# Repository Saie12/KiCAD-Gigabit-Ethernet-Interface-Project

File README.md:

# 🚀 High-Speed Gigabit Ethernet Interface

Welcome! This repository contains the complete hardware design files for a custom-built, 6-layer Gigabit Ethernet interface board.

The design is centered around the powerful **STM32F746NGH6** (an ARM Cortex-M7 MCU) and the **DP83867IR** Gigabit PHY. The entire layout was planned to meet strict high-speed design rules, featuring a robust multi-rail power supply and controlled impedance routing for 1Gbps performance.

## 🛠️ Key Features & Components

* **Brain (MCU):** `STM32F746NGH6` (ARM Cortex-M7)
* **Translator (PHY):** `DP83867IRPAPT` (10/100/1000 Mbps Gigabit PHY)
* **Data Interface:** `RGMII`
* **Port (Connector):** `ARJM11D7-502-AB-EW2` (A shielded Gigabit MagJack with integrated LEDs)
* **Power Supply:** 5V USB-C input, feeding a "power tree" of four independent LDOs for ultra-clean `+3.3V`, `+2.5V`, `+1.8V`, and `+1.1V` rails.
* **PCB:** Custom 6-layer, 80x50mm board with controlled impedance routing.
* **Debug:** Standard 10-pin ARM SWD (Serial Wire Debug) header.

## ✅ Hardware Project Status: Complete!

This repository covers the complete hardware design and manufacturing file generation. All phases of the hardware build are finished.

* ✅ **Phase 1: Component Selection**
    * *Selected and verified the core MCU, PHY, MagJack, and all power components for Gigabit-speed requirements.*
* ✅ **Phase 2: Schematic Design**
    * *Created the full electronic blueprint, connecting all components and defining all power and signal nets.*
* ✅ **Phase 3: Pre-Layout Checks**
    * *Ran a full Electrical Rules Check (ERC) and assigned all physical component footprints.*
* ✅ **Phase 4: PCB Layout**
    * *Designed the 6-layer stackup, floorplanned all components, poured all ground and power planes, and hand-routed all 17 critical high-speed differential and RGMII traces.*
* ✅ **Phase 5: Manufacturing File Generation**
    * *Generated the final Gerber and Drill files (`.zip`) required for fabrication.*

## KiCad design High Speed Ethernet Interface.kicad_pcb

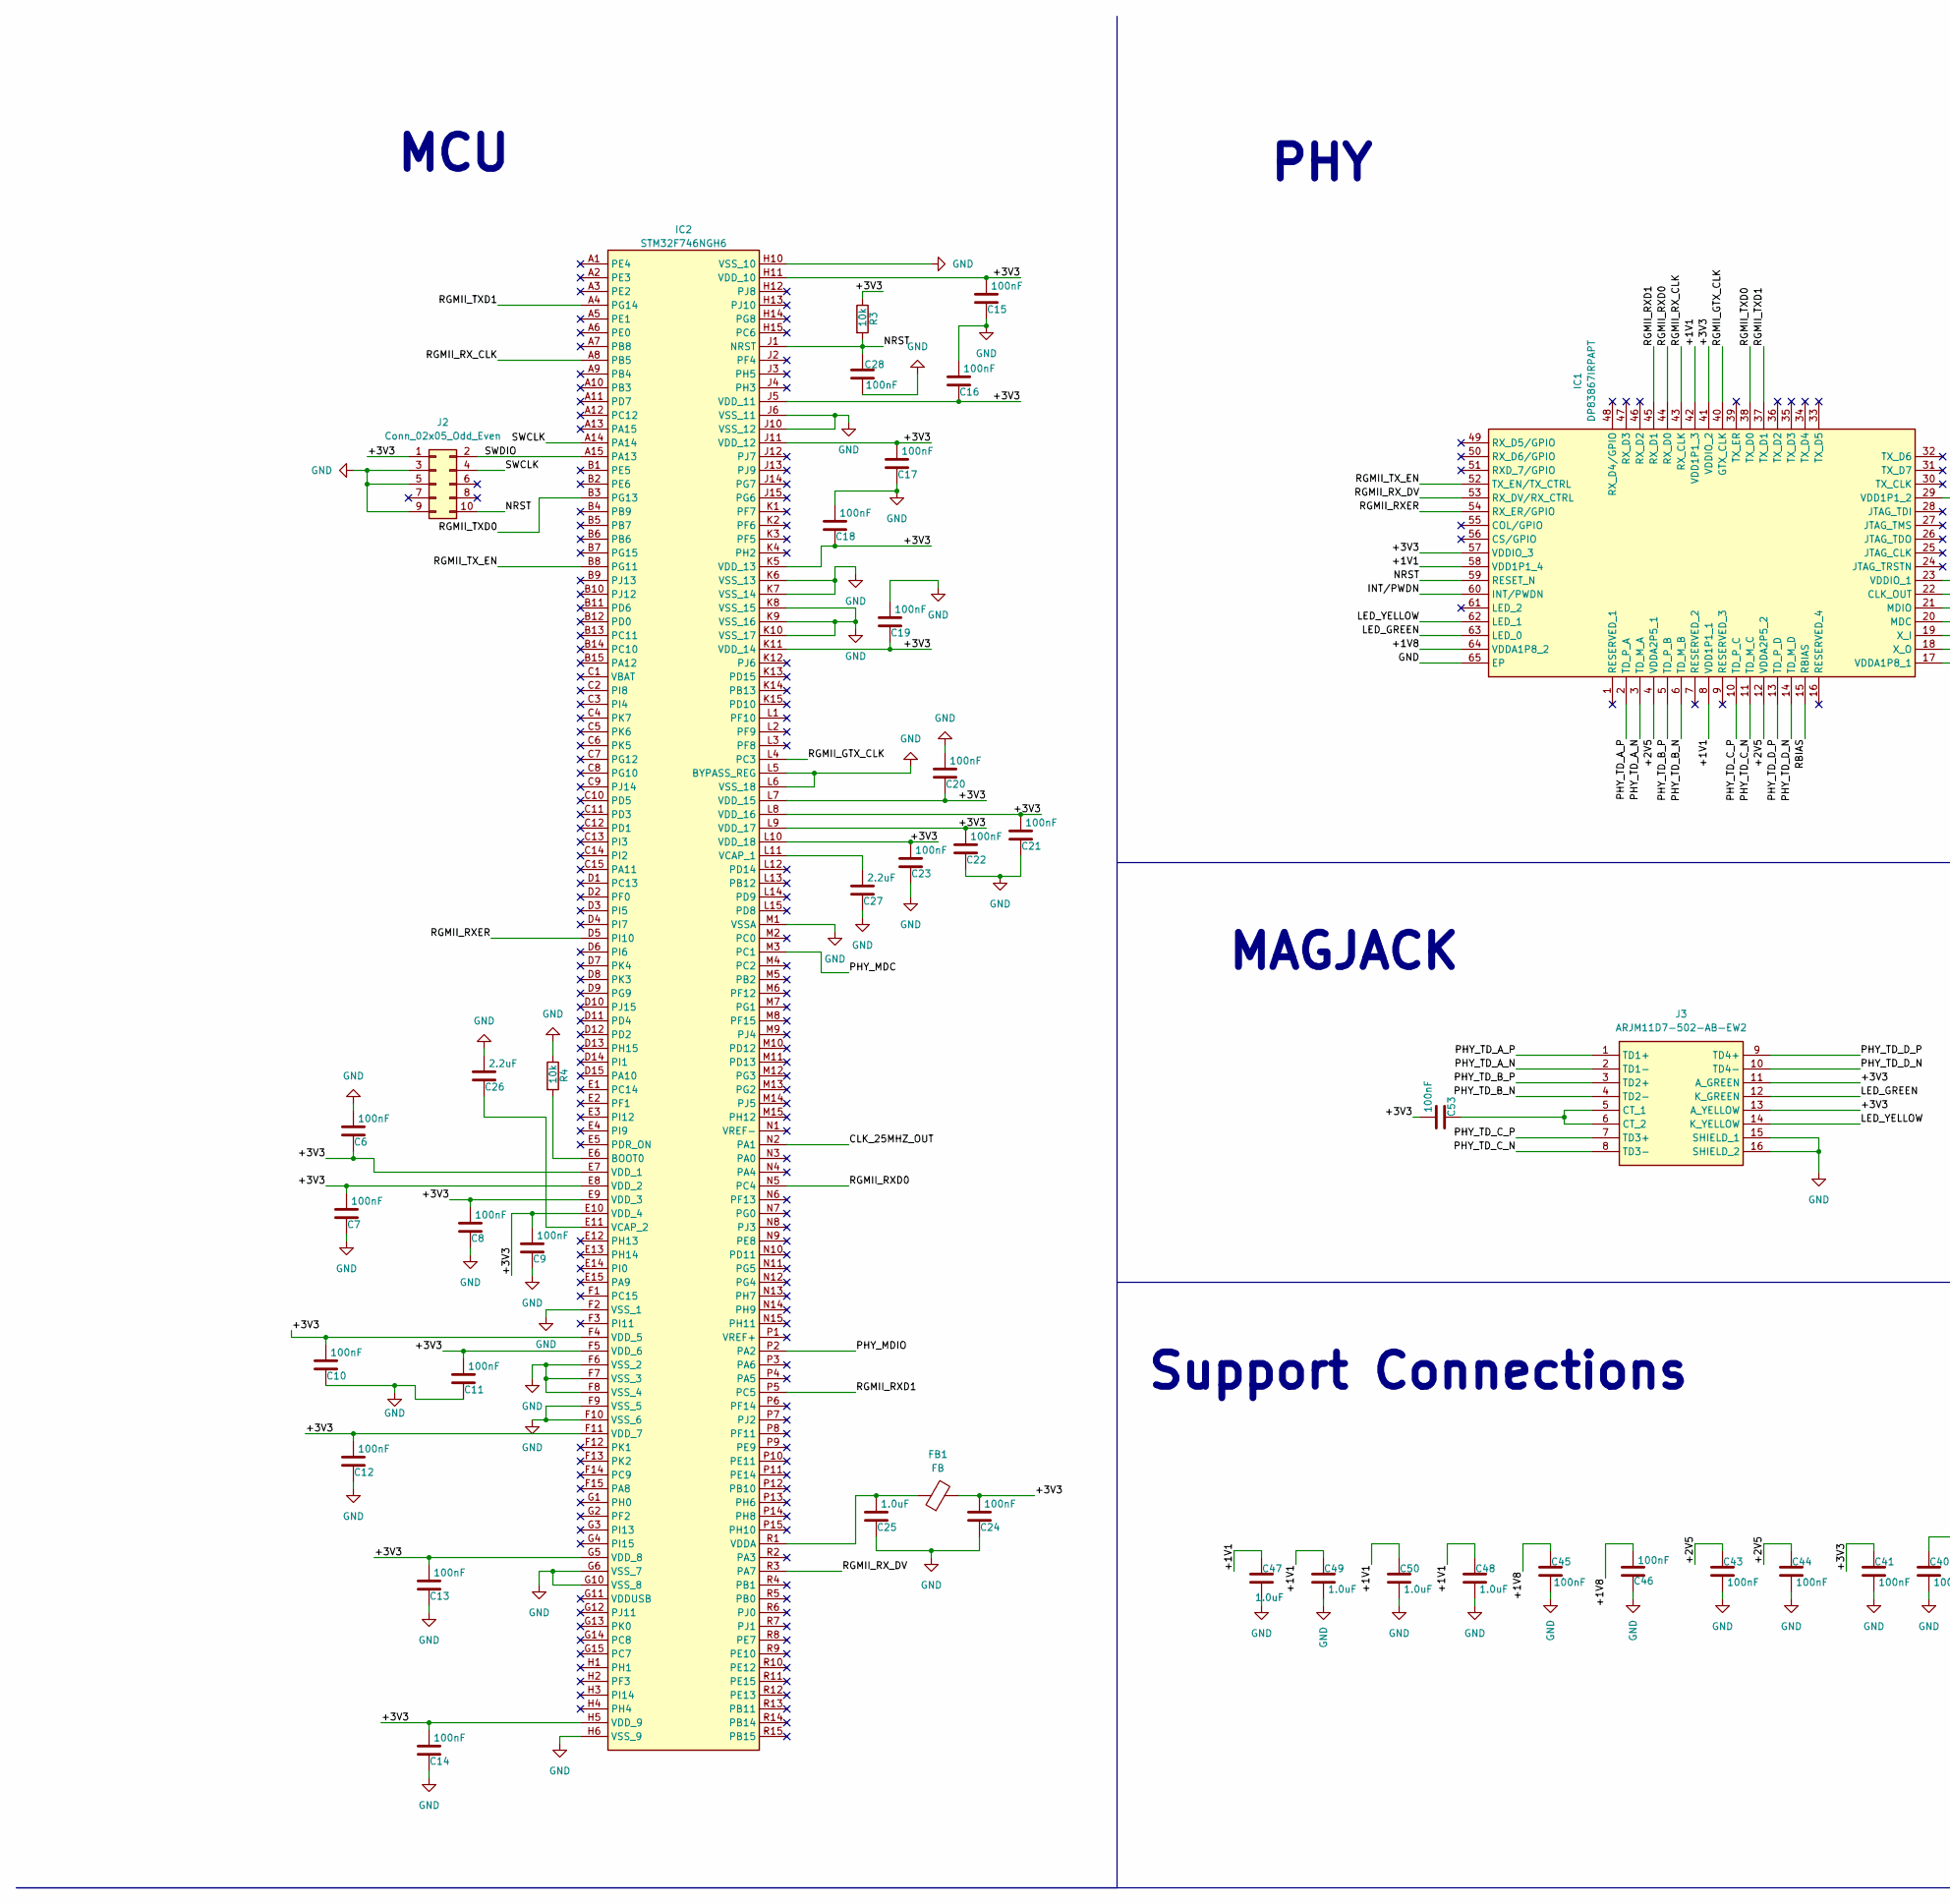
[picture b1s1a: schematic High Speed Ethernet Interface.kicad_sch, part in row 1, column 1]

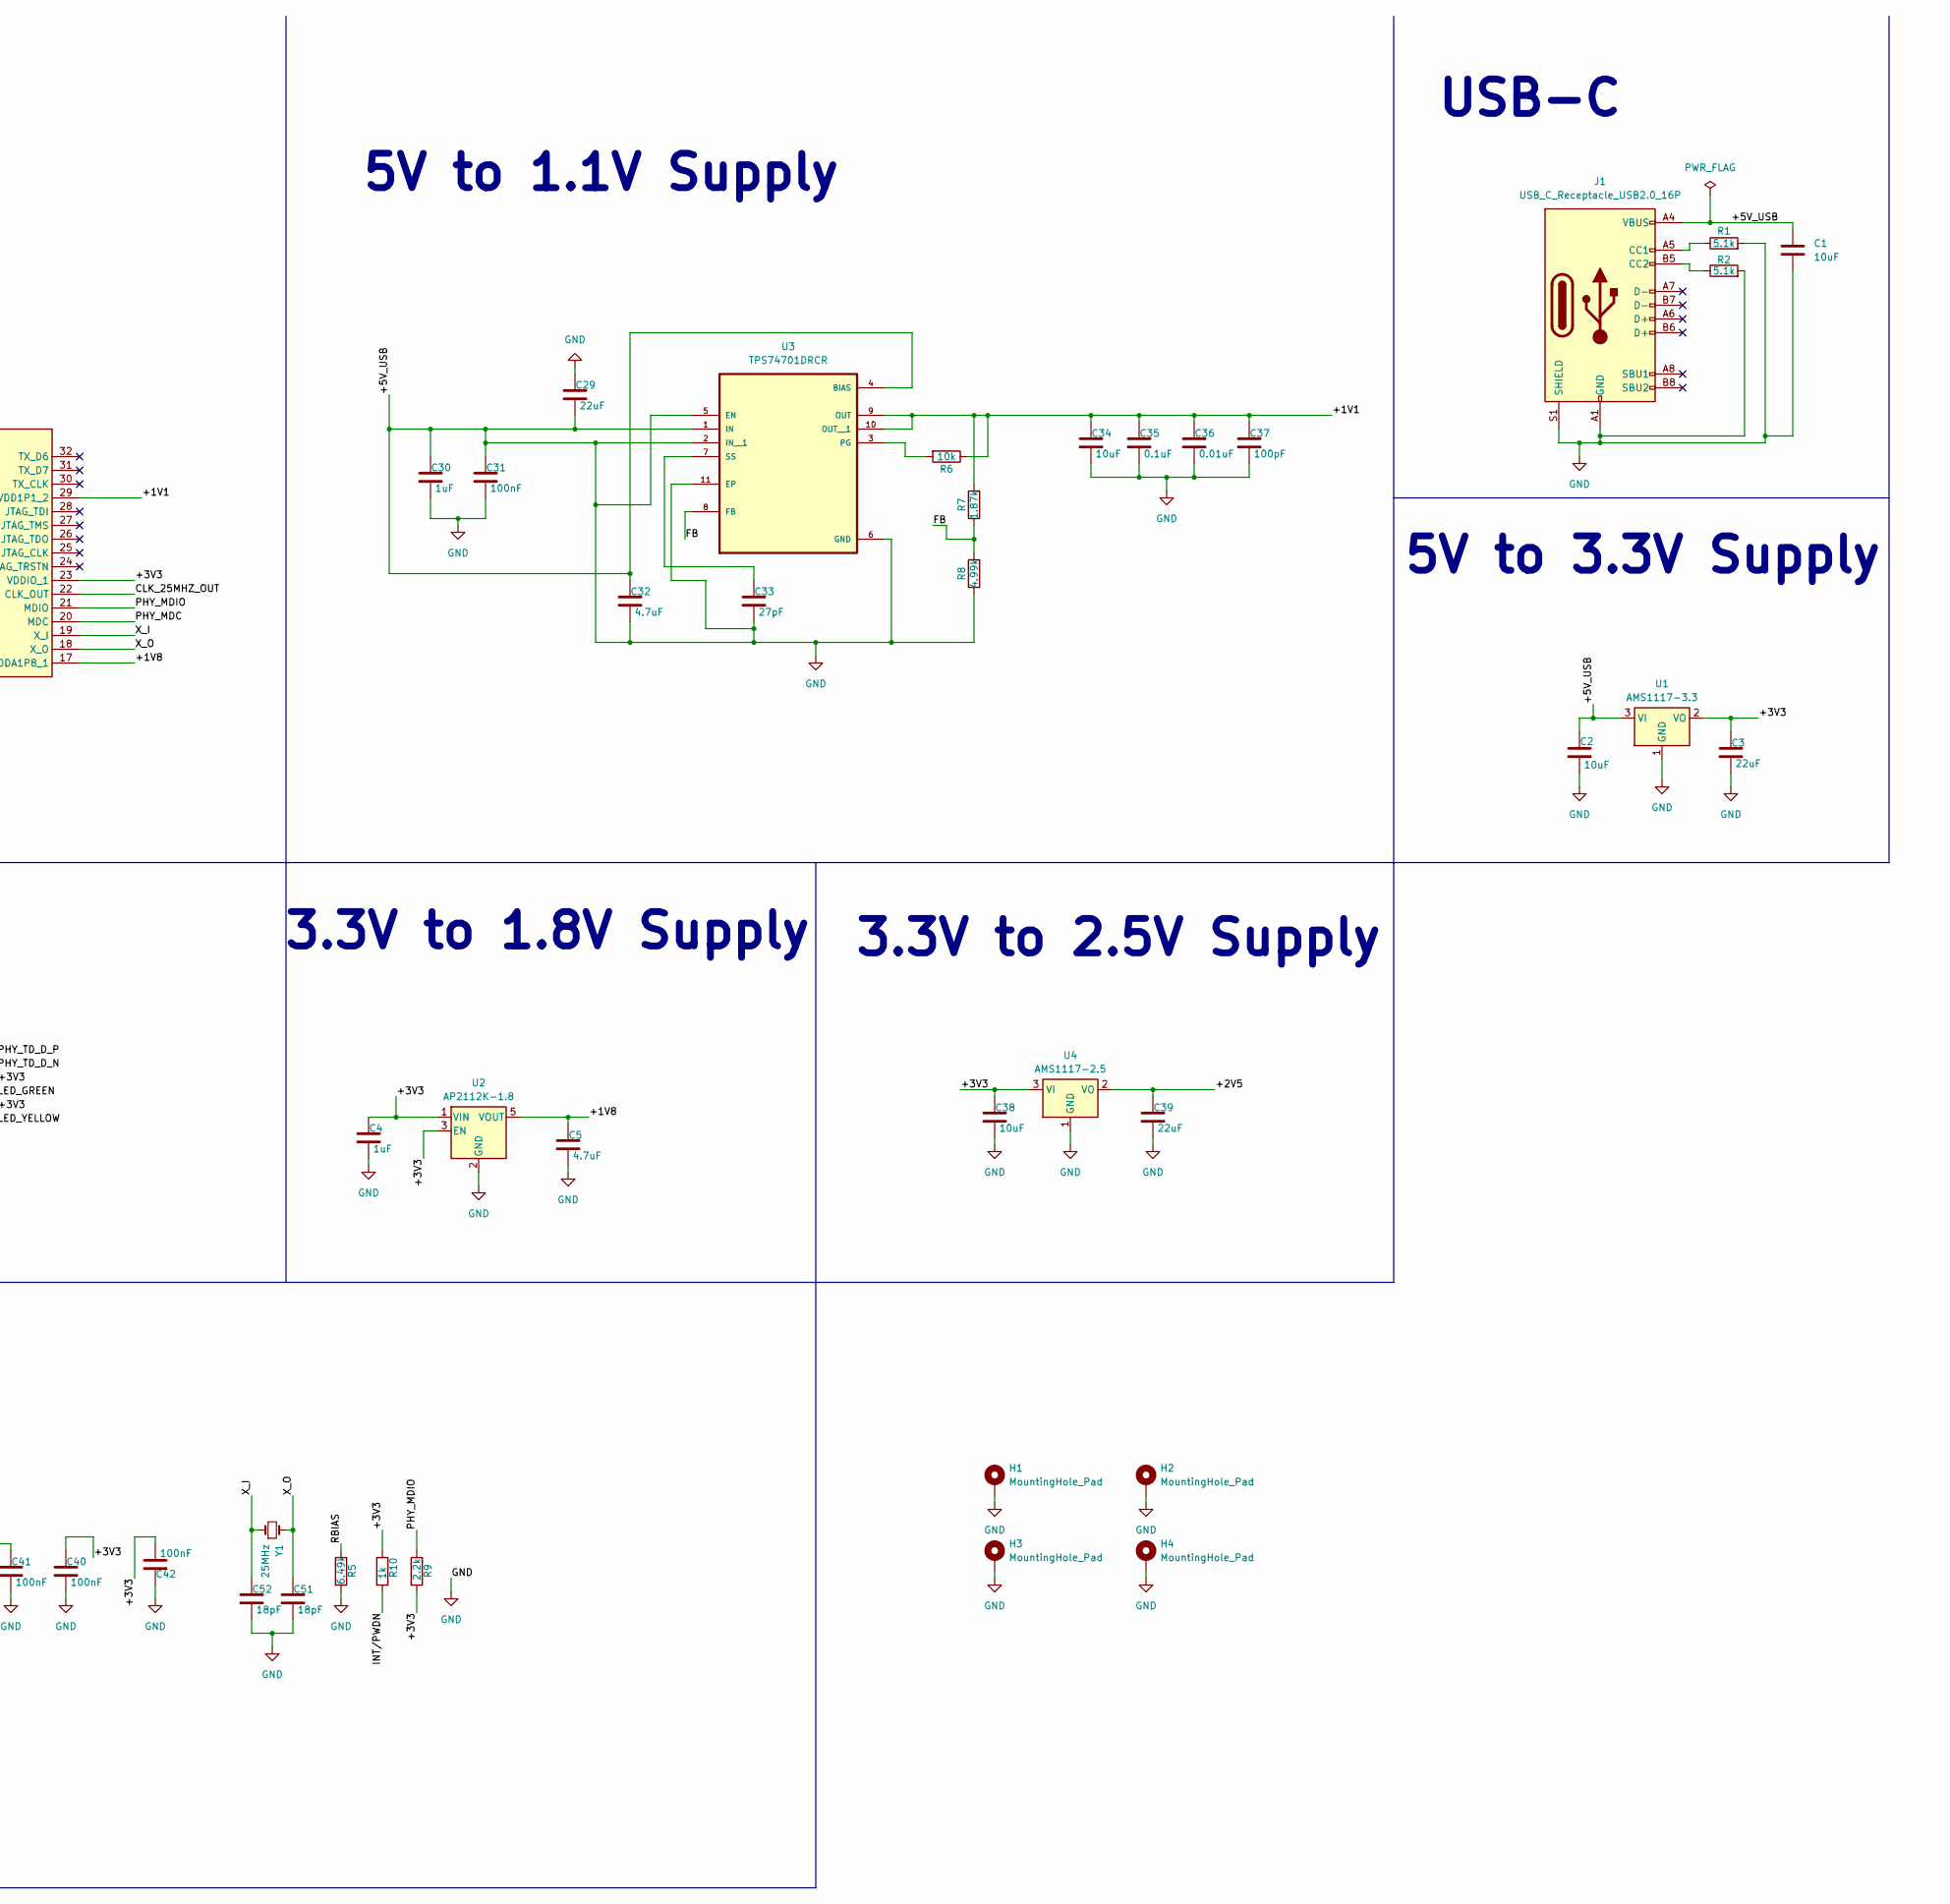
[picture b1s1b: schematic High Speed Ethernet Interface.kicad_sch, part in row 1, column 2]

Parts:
C1, C2, C34, C38: 10uF; C_1206_3216Metric
C3, C29, C39: 22uF; C_1206_3216Metric
C4, C30: 1uF; C_0805_2012Metric
C5, C32: 4.7uF; C_1206_3216Metric
C6, C7, C8, C9, C10, C11, C12, C13, C14, C15, C16, C17, C18, C19, C20, C21, C22, C23, C24, C28, C31, C40, C41, C42, C43, C44, C45, C46, C53: 100nF; C_0805_2012Metric
C25, C47, C48, C49, C50: 1.0uF; C_0805_2012Metric
C26, C27: 2.2uF; C_1206_3216Metric
C33: 27pF; C_0805_2012Metric
C35: 0.1uF; C_0805_2012Metric
C36: 0.01uF; C_0805_2012Metric
C37: 100pF; C_0805_2012Metric
C51, C52: 18pF; C_0805_2012Metric
FB1: FB; L_0805_2012Metric
H1, H2, H3, H4: MountingHole_Pad; MountingHole_3.2mm_M3_Pad
IC1: DP83867IRPAPT; Manufacturer_Part_Number DP83867IRPAPT; Mouser Part Number 595-DP83867IRPAPT
IC2: STM32F746NGH6; Manufacturer_Part_Number STM32F746NGH6; Mouser Part Number 511-STM32F746NGH6
J1: USB_C_Receptacle_USB2.0_16P; USB_C_Receptacle_HRO_TYPE-C-31-M-12
J2: Conn_02x05_Odd_Even; PinHeader_2x05_P1.27mm_Vertical
J3: ARJM11D7-502-AB-EW2; ARJM11D7502ABEW2; Manufacturer_Part_Number ARJM11D7-502-AB-EW2; Mouser Part Number 815-RJM11D7502ABEW2
R1, R2: 5.1k; R_0805_2012Metric
R3, R4, R6: 10k; R_0805_2012Metric
R5: 6.49k; R_0805_2012Metric
R7: 1.87k; R_0805_2012Metric
R8: 4.99k; R_0805_2012Metric
R9: 2.2k; R_0805_2012Metric
R10: 1k; R_0805_2012Metric
U1: AMS1117-3.3; SOT-223-3_TabPin2
U2: AP2112K-1.8; SOT-23-5
U3: TPS74701DRCR; VREG_V62_16624-01YE
U4: AMS1117-2.5; SOT-223-3_TabPin2
Y1: 25MHz; Crystal_SMD_3225-4Pin_3.2x2.5mm

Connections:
/+1V1: C34.1, C35.1, C36.1, C37.1, C47.1, C48.1, C49.1, C50.1, IC1.8 (VDD1P1_1), IC1.29 (VDD1P1_2), IC1.42 (VDD1P1_3), IC1.58 (VDD1P1_4), R6.1, R7.2, U3.9 (OUT), U3.10 (OUT__1)
/+1V8: C5.1, C45.1, C46.2, IC1.17 (VDDA1P8_1), IC1.64 (VDDA1P8_2), U2.5 (VOUT)
/+2V5: C39.1, C43.1, C44.1, IC1.4 (VDDA2P5_1), IC1.12 (VDDA2P5_2), U4.2 (VO)
/+3V3: C3.1, C4.1, C6.1, C7.2, C8.2, C9.2, C10.2, C11.2, C12.2, C13.2, C14.2, C15.2, C16.1, C17.2, C18.1, C19.1, C20.1, C21.2, C22.2, C23.2, C24.2, C38.1, C40.1, C41.1, C42.2, C53.2, FB1.2, IC1.23 (VDDIO_1), IC1.41 (VDDIO_2), IC1.57 (VDDIO_3), IC2.E7 (VDD_1), IC2.E8 (VDD_2), IC2.E9 (VDD_3), IC2.E10 (VDD_4), IC2.F4 (VDD_5), IC2.F5 (VDD_6), IC2.F11 (VDD_7), IC2.G5 (VDD_8), IC2.H5 (VDD_9), IC2.H11 (VDD_10), IC2.J5 (VDD_11), IC2.J11 (VDD_12), IC2.K5 (VDD_13), IC2.K11 (VDD_14), IC2.L7 (VDD_15), IC2.L8 (VDD_16), IC2.L9 (VDD_17), IC2.L10 (VDD_18), J2.1, J3.11 (A_GREEN), J3.13 (A_YELLOW), R3.1, R9.2, R10.1, U1.2 (VO), U2.1 (VIN), U2.3 (EN), U4.3 (VI)
/CLK_25MHZ_OUT: IC1.22 (CLK_OUT), IC2.N2 (PA1)
/FB: R7.1, R8.2, U3.8 (FB)
/INT/PWDN: IC1.60 (INT/PWDN), R10.2
/LED_GREEN: IC1.63 (LED_0), J3.12 (K_GREEN)
/LED_YELLOW: IC1.62 (LED_1), J3.14 (K_YELLOW)
/NRST: C28.1, IC1.59 (RESET_N), IC2.J1 (NRST), J2.10, R3.2
/PHY_MDC: IC1.20 (MDC), IC2.M3 (PC1)
/PHY_MDIO: IC1.21 (MDIO), IC2.P2 (PA2), R9.1
/PHY_TD_A_N: IC1.3 (TD_M_A), J3.2 (TD1-)
/PHY_TD_A_P: IC1.2 (TD_P_A), J3.1 (TD1+)
/PHY_TD_B_N: IC1.6 (TD_M_B), J3.4 (TD2-)
/PHY_TD_B_P: IC1.5 (TD_P_B), J3.3 (TD2+)
/PHY_TD_C_N: IC1.11 (TD_M_C), J3.8 (TD3-)
/PHY_TD_C_P: IC1.10 (TD_P_C), J3.7 (TD3+)
/PHY_TD_D_N: IC1.14 (TD_M_D), J3.10 (TD4-)
/PHY_TD_D_P: IC1.13 (TD_P_D), J3.9 (TD4+)
/RBIAS: IC1.15 (RBIAS), R5.1
/RGMII_GTX_CLK: IC1.40 (GTX_CLK), IC2.L4 (PC3)
/RGMII_RXD0: IC1.44 (RX_D0), IC2.N5 (PC4)
/RGMII_RXD1: IC1.45 (RX_D1), IC2.P5 (PC5)
/RGMII_RXER: IC1.54 (RX_ER/GPIO), IC2.D5 (PI10)
/RGMII_RX_CLK: IC1.43 (RX_CLK), IC2.A8 (PB5)
/RGMII_RX_DV: IC1.53 (RX_DV/RX_CTRL), IC2.R3 (PA7)
/RGMII_TXD0: IC1.38 (TX_D0), IC2.B3 (PG13)
/RGMII_TXD1: IC1.37 (TX_D1), IC2.A4 (PG14)
/RGMII_TX_EN: IC1.52 (TX_EN/TX_CTRL), IC2.B8 (PG11)
/SWCLK: IC2.A14, J2.4
/SWDIO: IC2.A15 (PA13), J2.2
/X_I: C52.1, IC1.19 (X_I), Y1.1
/X_O: C51.1, IC1.18 (X_O), Y1.2
GND: C1.1, C1.2, C2.1, C2.2, C3.2, C4.2, C5.2, C6.2, C7.1, C8.1, C9.1, C10.1, C11.1, C12.1, C13.1, C14.1, C15.1, C16.2, C17.1, C18.2, C19.2, C20.2, C21.1, C22.1, C23.1, C24.1, C25.1, C26.2, C27.1, C28.2, C29.1, C29.2, C30.1, C30.2, C31.1, C31.2, C32.1, C32.2, C33.2, C34.2, C35.2, C36.2, C37.2, C38.2, C39.2, C40.2, C41.2, C42.1, C43.2, C44.2, C45.2, C46.1, C47.2, C48.2, C49.2, C50.2, C51.2, C52.2, H1.1, H2.1, H3.1, H4.1, IC1.65 (EP), IC2.F2 (VSS_1), IC2.F6 (VSS_2), IC2.F7 (VSS_3), IC2.F8 (VSS_4), IC2.F9 (VSS_5), IC2.F10 (VSS_6), IC2.G6 (VSS_7), IC2.G10 (VSS_8), IC2.H6 (VSS_9), IC2.H10 (VSS_10), IC2.J6 (VSS_11), IC2.J10 (VSS_12), IC2.K6 (VSS_13), IC2.K7 (VSS_14), IC2.K8 (VSS_15), IC2.K9 (VSS_16), IC2.K10 (VSS_17), IC2.L5 (BYPASS_REG), IC2.L6 (VSS_18), IC2.M1 (VSSA), J1.A1 (GND), J1.A4 (VBUS), J1.A9 (VBUS), J1.A12 (GND), J1.B1 (GND), J1.B4 (VBUS), J1.B9 (VBUS), J1.B12 (GND), J1.S1 (SHIELD), J2.3, J2.5, J2.9, J3.15 (SHIELD_1), J3.16 (SHIELD_2), R1.2, R2.2, R4.1, R5.2, R8.1, U1.1 (GND), U1.3 (VI), U2.2 (GND), U3.1 (IN), U3.2 (IN__1), U3.4 (BIAS), U3.5 (EN), U3.6 (GND), U3.11 (EP), U3.12, U3.13, U3.14, U3.15, U4.1 (GND)
unnamed: IC2.E6 (BOOT0), R4.2
unnamed: C27.2, IC2.L11 (VCAP_1)
unnamed: C26.1, IC2.E11 (VCAP_2)
unnamed: C25.2, FB1.1, IC2.R1 (VDDA)
unnamed: J1.A5 (CC1), R1.1
unnamed: J1.B5 (CC2), R2.1
unnamed: C53.1, J3.5 (CT_1), J3.6 (CT_2)
unnamed: R6.2, U3.3 (PG)
unnamed: C33.1, U3.7 (SS)

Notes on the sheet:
Support Connections
5V to 3.3V Supply
PHY
USB-C
5V to 1.1V Supply
MAGJACK
MCU
3.3V to 1.8V Supply
3.3V to 2.5V Supply

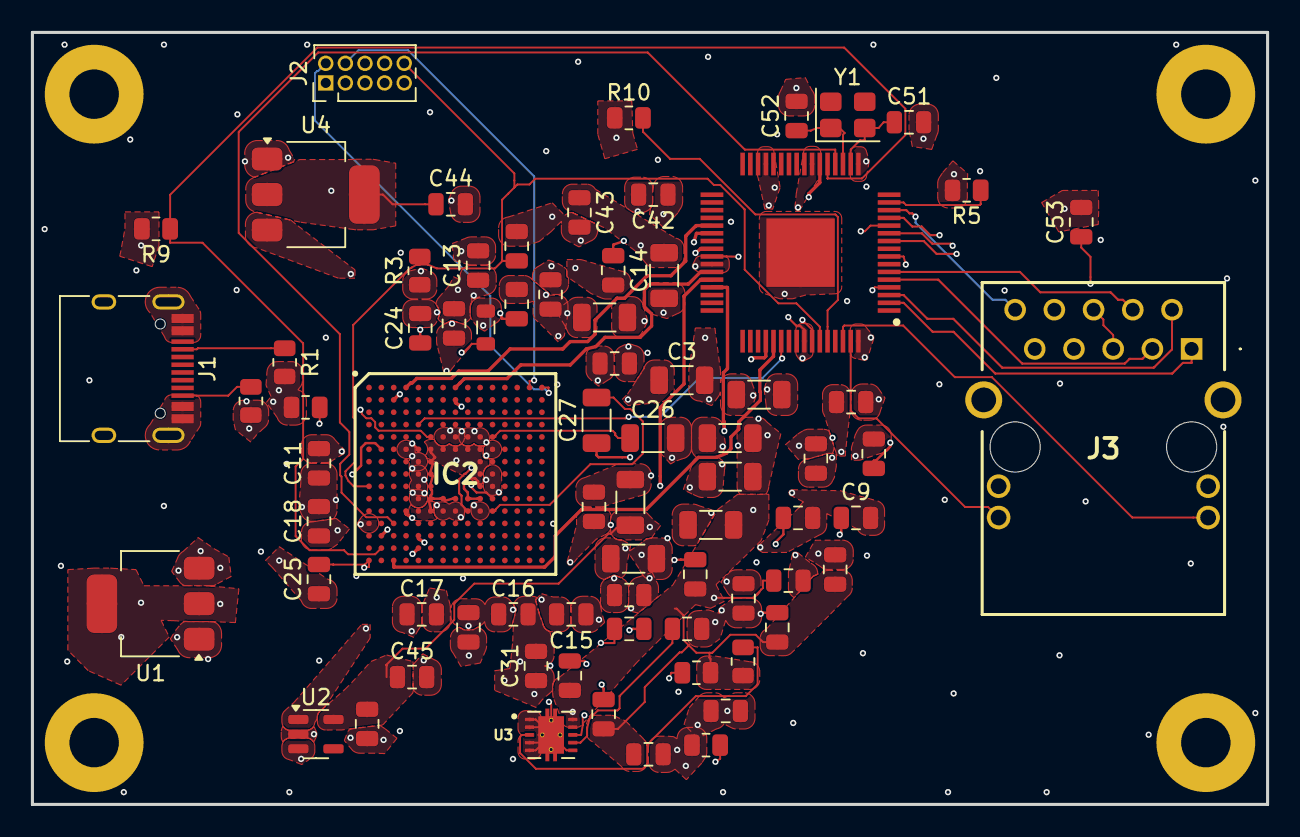
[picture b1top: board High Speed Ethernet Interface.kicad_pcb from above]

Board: 6 copper layers, 80.0 x 50.0 mm, 78 parts (0 on the bottom side), 44 nets.

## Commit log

2025-11-17 Initial commit of Gigabit Ethernet project
2025-11-17 Add MIT License to the project
2025-11-17 Add README for Gigabit Ethernet Interface project
    This README provides an overview of the hardware design files for a custom-built Gigabit Ethernet interface board, detailing its components, features, and project status.
